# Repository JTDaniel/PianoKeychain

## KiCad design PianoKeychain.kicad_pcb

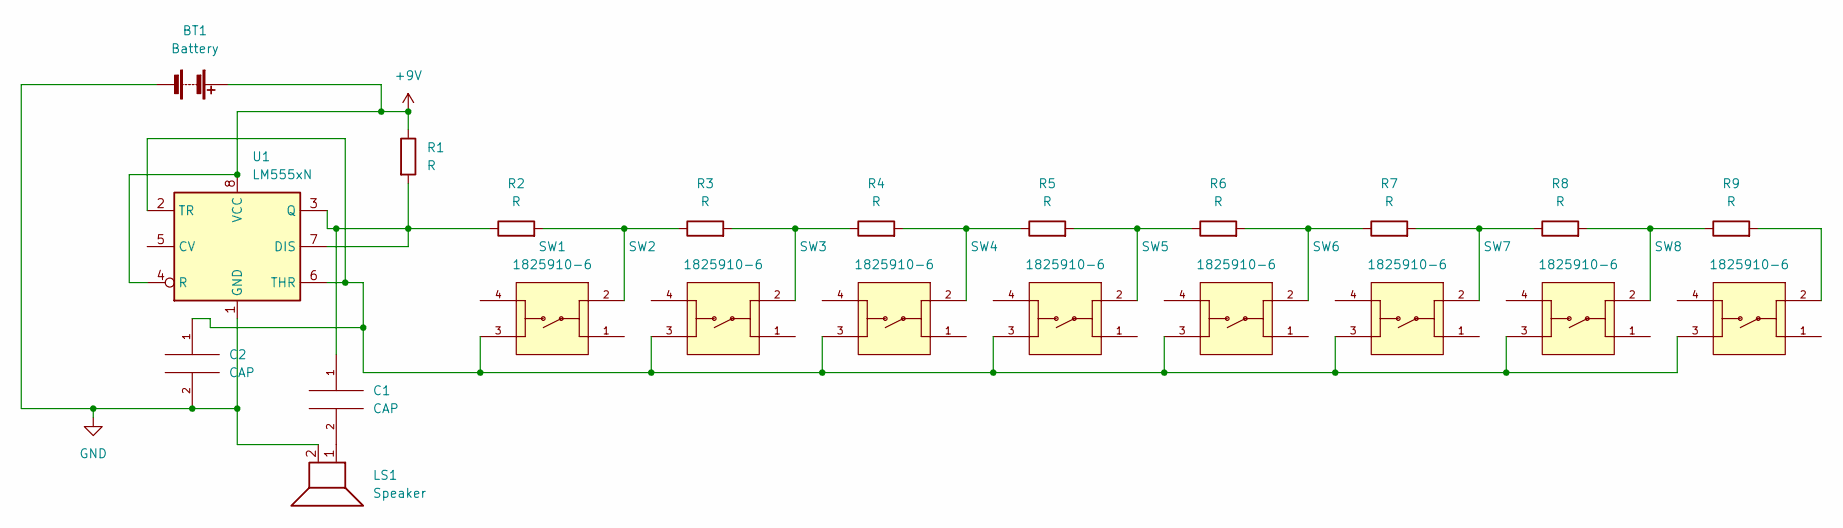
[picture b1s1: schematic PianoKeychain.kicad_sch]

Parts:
BT1: Battery; PinSocket_1x02_P2.54mm_Vertical
C1, C2: CAP; CP_Axial_L10.0mm_D4.5mm_P15.00mm_Horizontal
LS1: Speaker; Buzzer_15x7.5RM7.6
R1, R2, R3, R4, R5, R6, R7, R8, R9: R; R_Axial_DIN0204_L3.6mm_D1.6mm_P7.62mm_Horizontal
SW1, SW2, SW3, SW4, SW5, SW6, SW7, SW8: 1825910-6; SW_1825910-6-4
U1: LM555xN; DIP-8_W7.62mm

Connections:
+9V: BT1.1 (+), R1.1, U1.4 (R), U1.8 (VCC)
GND: BT1.2 (-), C2.2, LS1.2, U1.1 (GND)
unnamed: C1.1, R1.2, R2.1, U1.3 (Q), U1.7 (DIS)
unnamed: C1.2, LS1.1
unnamed: C2.1, SW1.3, SW2.3, SW3.3, SW4.3, SW5.3, SW6.3, SW7.3, SW8.3, U1.2 (TR), U1.6 (THR)
unnamed: R2.2, R3.1, SW1.2
unnamed: R3.2, R4.1, SW2.2
unnamed: R4.2, R5.1, SW3.2
unnamed: R5.2, R6.1, SW4.2
unnamed: R6.2, R7.1, SW5.2
unnamed: R7.2, R8.1, SW6.2
unnamed: R8.2, R9.1, SW7.2
unnamed: R9.2, SW8.2

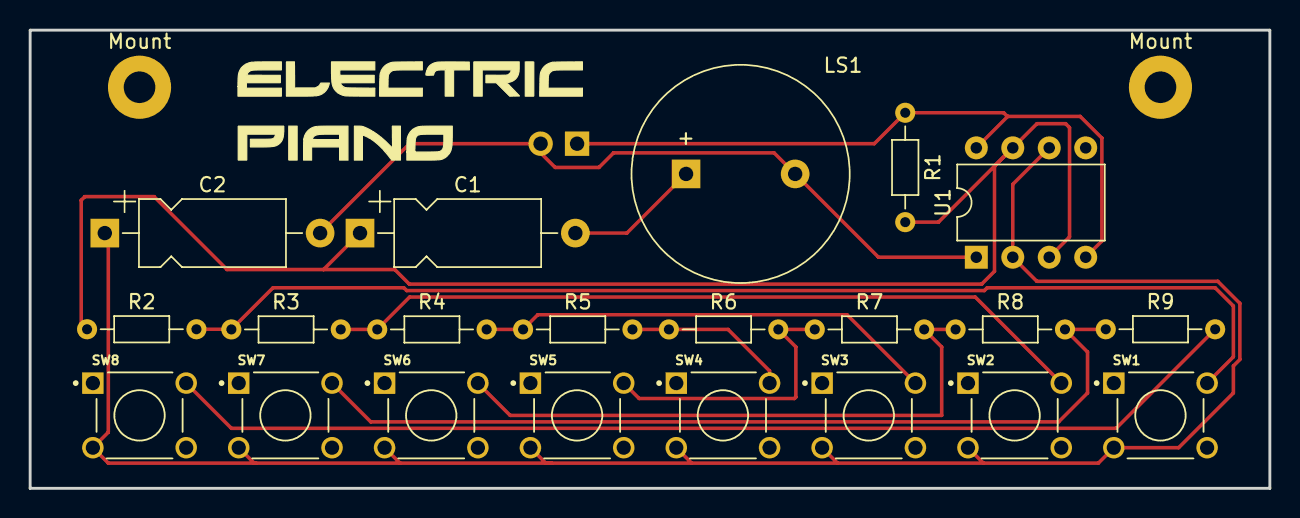
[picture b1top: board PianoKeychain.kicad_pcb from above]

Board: 2 copper layers, 86.4 x 31.9 mm, 24 parts (1 on the bottom side), 13 nets.

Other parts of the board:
Mount: MountingHole_2.2mm_M2_Pad
Mount#2: Mounting Hole; MountingHole_2.2mm_M2_Pad

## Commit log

2022-08-03 Creation of new project, Piano keychain, project was designed for use in the ASU makerspace in order to teach soldering workshops.
2022-08-03 Reoranized Repo
2022-08-03 Added 3d FreeCad files for the keychain case
2022-08-11 Updated case 3d model to exclude key ring, changed silkscreen
2022-08-19 routine update
